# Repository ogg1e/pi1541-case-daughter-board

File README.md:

# pi1541-case-daughter-board
image:

Makes it a little easier to wire and install the buttons/leds.

This is a daughter board to be used in the case found here:
https://www.thingiverse.com/thing:3329176

This uses standard 6x6mm push button switches and 1x4 and 1x8 2.54mm pitch headers.

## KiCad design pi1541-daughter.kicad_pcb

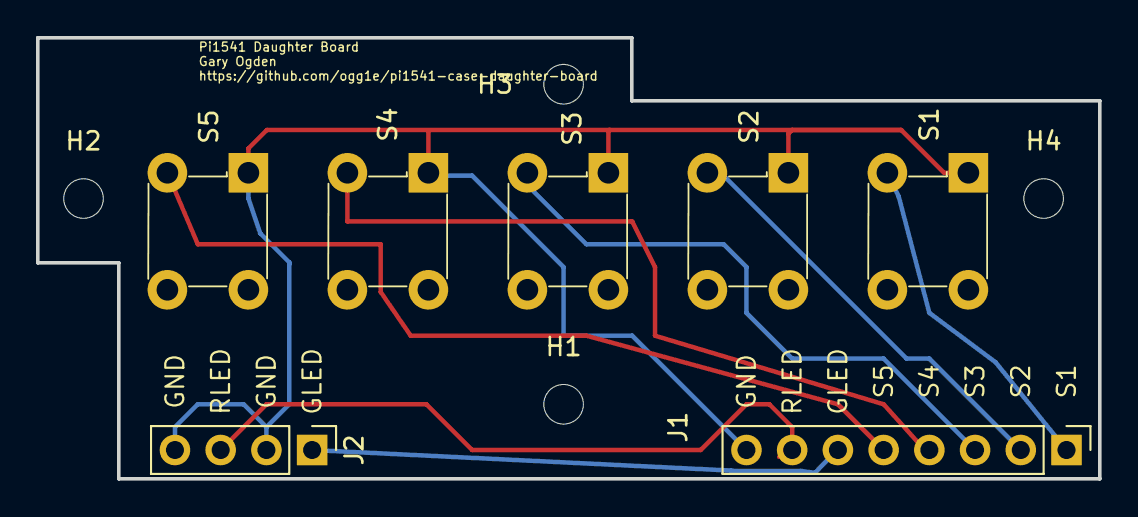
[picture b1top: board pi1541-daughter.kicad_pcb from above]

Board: 2 copper layers, 59.0 x 24.5 mm, 11 parts (0 on the bottom side), 8 nets.

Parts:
H1, H2, H3, H4: MountingHole; MountingHole_2.2mm_M2
J1: toPi; Pin_Header_Straight_1x08_Pitch2.54mm
J2: LEDs; Pin_Header_Straight_1x04_Pitch2.54mm
S1, S2, S3, S4, S5: 1825910-6; Switch_Tactile_THT_6x6mm

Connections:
unnamed: J1.1, S1.3
unnamed: J1.2, S2.3
unnamed: J1.3, S3.3
unnamed: J1.4, S4.3
unnamed: J1.5, S5.3
unnamed: J1.6, J2.1
unnamed: J1.7, J2.3
unnamed: J1.8, J2.2, J2.4, S1.1, S2.1, S3.1, S4.1, S5.1

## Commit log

2018-11-13 ignore file
2018-11-13 added kicad files
2018-11-14 added image
2018-11-14 updated image

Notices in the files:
pi1541-daughter.kicad_pcb:
License: CC By 4.0
